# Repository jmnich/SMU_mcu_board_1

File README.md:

# SMU_mcu_board_1

MCU module for HtBlog Source Measure Unit

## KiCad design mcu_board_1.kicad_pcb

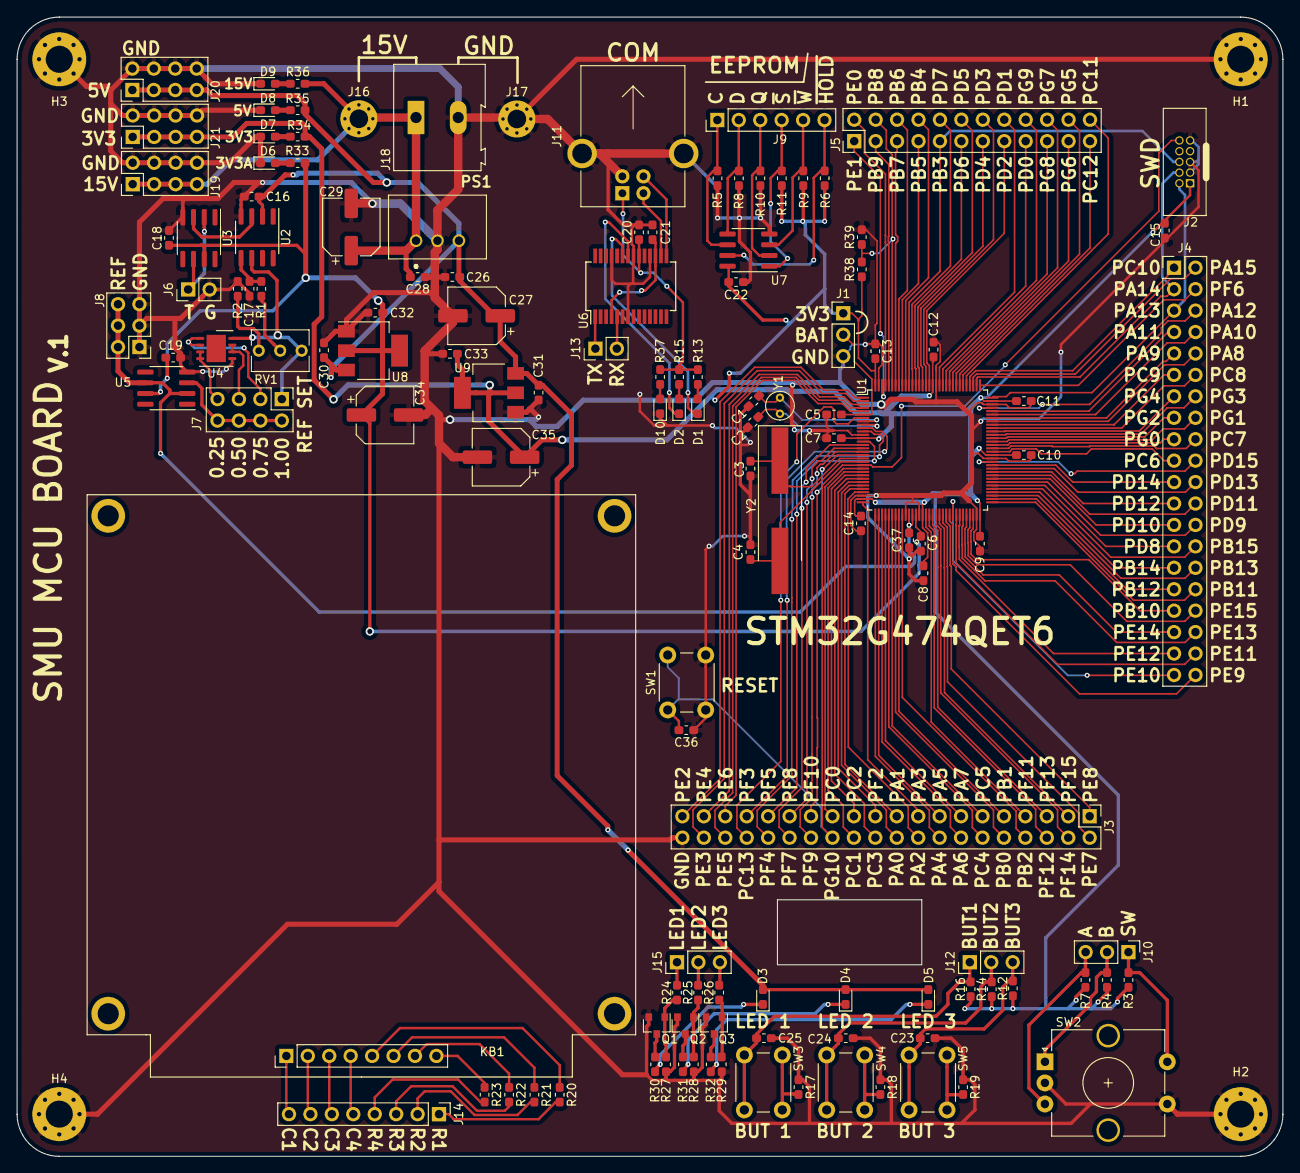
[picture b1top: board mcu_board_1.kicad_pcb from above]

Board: 2 copper layers, 150.0 x 135.0 mm, 133 parts (0 on the bottom side), 178 nets.

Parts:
C1, C2: 12p; C_0603_1608Metric_Pad1.05x0.95mm_HandSolder
C3, C4: 18p; C_0603_1608Metric_Pad1.05x0.95mm_HandSolder
C5, C15, C16, C17, C18, C19, C20, C21, C26, C28, C30, C31, C32, C33: 1u; C_0603_1608Metric_Pad1.05x0.95mm_HandSolder
C6, C7, C8, C9, C10, C11, C12, C13, C14, C22, C23, C24, C25, C36: 100n; C_0603_1608Metric_Pad1.05x0.95mm_HandSolder
C27, C29: 56u 25V; CP_Elec_6.3x5.9
C34, C35: 6.8u 25V; CP_Elec_6.3x5.9
C37: 1U; C_0603_1608Metric_Pad1.05x0.95mm_HandSolder
D1: R; LED_0603_1608Metric_Pad1.05x0.95mm_HandSolder
D2, D3, D4, D5: B; LED_0603_1608Metric_Pad1.05x0.95mm_HandSolder
D6, D7, D8, D9: LED G; LED_0603_1608Metric_Pad1.05x0.95mm_HandSolder
D10: G; LED_0603_1608Metric_Pad1.05x0.95mm_HandSolder
H1, H2, H3, H4: MountingHole_Pad; MountingHole_3.2mm_M3_Pad_Via
J1, J10, J12, J15: Conn_01x03; PinHeader_1x03_P2.54mm_Vertical
J2: ARM_SWD_10; JTAG_10pin_1.27_socket
J3, J4: Conn_02x20_Odd_Even; PinHeader_2x20_P2.54mm_Vertical
J5: Conn_02x12_Odd_Even; PinHeader_2x12_P2.54mm_Vertical
J6, J13: Conn_01x02; PinHeader_1x02_P2.54mm_Vertical
J7, J19, J20, J21: Conn_02x04_Odd_Even; PinHeader_2x04_P2.54mm_Vertical
J8: Conn_02x03_Odd_Even; PinHeader_2x03_P2.54mm_Vertical
J9: Conn_01x06; PinHeader_1x06_P2.54mm_Vertical
J11: USB-B_WE_61400416121; USB_B_Horizontal
J14: Conn_01x08; PinHeader_1x08_P2.54mm_Vertical
J16: +15V; MountingHole_2.2mm_M2_Pad_Via
J17: GND; MountingHole_2.2mm_M2_Pad_Via
J18: WE 691216710002; Terminal_block_WE691216710002
KB1: AK-1604-N; AK-1604-N-BBW
PS1: 173950536
Q1, Q2, Q3: 2N7002BK,215; SOT-23
R1: 470k 1%; R_0603_1608Metric_Pad1.05x0.95mm_HandSolder
R2, R17, R18, R19, R24, R25, R26: 1k 1%; R_0603_1608Metric_Pad1.05x0.95mm_HandSolder
R3, R4, R5, R6, R7, R8, R9, R10, R11, R12, R14, R16, R20, R21, R22, R23, R27, R28, R29, R39: 47k 1%; R_0603_1608Metric_Pad1.05x0.95mm_HandSolder
R13, R15, R30, R31, R32, R37: 10k 1%; R_0603_1608Metric_Pad1.05x0.95mm_HandSolder
R33, R35: 6k8; R_0603_1608Metric_Pad1.05x0.95mm_HandSolder
R34: 4k7; R_0603_1608Metric_Pad1.05x0.95mm_HandSolder
R36: 20k; R_0603_1608Metric_Pad1.05x0.95mm_HandSolder
R38: DNP; R_0603_1608Metric_Pad1.05x0.95mm_HandSolder
RV1: 10k; Potentiometer_Vishay_T73XW_Horizontal
SW1, SW3, SW4, SW5: SW_SPST; SW_PUSH_6mm_H4.3mm
SW2: Rotary_Encoder_Switch; RotaryEncoder_Alps_EC12E-Switch_Vertical_H20mm_CircularMoun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
U1: STM32G474QET6; LQFP-128_14x14mm_P0.4mm
U2: REF5040; SOIC-8_3.9x4.9mm_P1.27mm
U3, U5: OPA333AID; SOIC-8_3.9x4.9mm_P1.27mm
U4: 50k 0.1%; DFN-8-1EP_4x4mm_P0.8mm_EP2.3x3.24mm
U6: FT232RL; SSOP-28_5.3x10.2mm_P0.65mm
U7: M95M01-R; SOIC-8_3.9x4.9mm_P1.27mm
U8, U9: AMS1117-3.3; SOT-223-3_TabPin2
Y1: 32.7680kHz; Crystal_C38-LF_D3.0mm_L8.0mm_Vertical
Y2: 10MHz; Crystal_SMD_HC49-SD_HandSoldering

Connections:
+3.3VA: C6.2, C18.2, C19.2, C32.1, C34.1, R33.1, U1.45, U3.7, U5.7, U8.2
+3V3: C7.2, C8.2, C9.2, C10.2, C11.2, C12.2, C13.2, C14.2, C15.1, C22.1, C33.1, C35.1, J1.1, J2.1, J21.1, J21.3, J21.5, J21.7, R3.1, R4.1, R6.1, R7.1, R9.1, R11.1, R12.1, R14.1, R16.1, R34.1, R38.1, U1.13, U1.31, U1.47, U1.64, U1.79, U1.95, U1.111, U1.128, U7.8, U9.2
+5V: C16.1, C26.1, C27.1, C30.1, C31.1, D3.2, D4.2, D5.2, J20.1, J20.3, J20.5, J20.7, PS1.3, R35.1, U2.2, U8.3, U9.3
+15V: C28.2, C29.1, J16.1, J18.1, J19.1, J19.3, J19.5, J19.7, PS1.1, R36.1
/Analog/1_4_REF: J7.7, U4.3, U4.4
/Analog/2_4_REF: J7.5, U4.6, U4.7
/Analog/3_4_REF: J7.3, U4.1, U4.2
/Analog/REF: J7.1, RV1.1, U2.6, U4.8
/REF: C37.2, J8.2, J8.4, J8.6, U1.43, U1.44, U5.2, U5.6
GND: C1.2, C2.2, C3.2, C4.2, C5.1, C6.1, C7.1, C8.1, C9.1, C10.1, C11.1, C12.1, C13.1, C14.1, C15.2, C16.2, C17.2, C18.1, C19.1, C20.2, C21.2, C22.2, C23.2, C24.2, C25.2, C26.2, C27.2, C28.1, C29.2, C30.2, C31.2, C32.2, C33.2, C34.2, C35.2, C36.1, C37.1, D6.1, D7.1, D8.1, D9.1, D10.1, H1.1, H2.1, H3.1, H4.1, J1.3, J2.3, J2.5, J2.9, J3.40, J6.2, J8.1, J8.3, J8.5, J11.4, J11.5, J17.1, J18.2, J19.2, J19.4, J19.6, J19.8, J20.2, J20.4, J20.6, J20.8, J21.2, J21.4, J21.6, J21.8, PS1.2, Q1.2, Q2.2, Q3.2, R2.2, R5.1, R8.1, R10.1, R17.1, R18.1, R19.1, R27.2, R28.2, R29.2, R39.2, SW1.2, SW2.C, SW2.S2, U1.12, U1.30, U1.42, U1.46, U1.63, U1.78, U1.94, U1.110, U1.127, U2.4, U3.4, U4.5, U5.4, U6.7, U6.18, U6.21, U6.25, U7.4, U8.1, U9.1
unnamed: C1.1, U1.8, Y1.1
unnamed: C2.1, U1.9, Y1.2
unnamed: C3.1, U1.19, Y2.1
unnamed: C4.1, U1.20, Y2.2
unnamed: C5.2, J1.2, U1.6
unnamed: C17.1, R1.1, U2.5
unnamed: C20.1, J11.1, R13.1, R15.1, R37.1, U6.20
unnamed: C21.1, U6.4, U6.17
unnamed: C23.1, J12.3, R12.2, SW5.1
unnamed: C24.1, J12.2, R14.2, SW4.1
unnamed: C25.1, J12.1, R16.2, SW3.1
unnamed: D1.1, U6.23
unnamed: D1.2, R13.2
unnamed: D2.1, U6.22
unnamed: D2.2, R15.2
unnamed: D3.1, R30.1
unnamed: D4.1, R31.1
unnamed: D5.1, R32.1
unnamed: D6.2, R33.2
unnamed: D7.2, R34.2
unnamed: D8.2, R35.2
unnamed: D9.2, R36.2
unnamed: D10.2, R37.2
unnamed: J6.1, U3.2, U3.6
unnamed: J7.2, J7.4, J7.6, J7.8, U5.3
unnamed: J9.1, R5.2, U7.6
unnamed: J9.2, R8.2, U7.5
unnamed: J9.3, R10.2, U7.2
unnamed: J9.4, R11.2, U7.1
unnamed: J9.5, R9.2, U7.3
unnamed: J9.6, R6.2, U7.7
unnamed: J10.1, R3.2, SW2.S1
unnamed: J10.2, R4.2, SW2.A
unnamed: J10.3, R7.2, SW2.B
unnamed: J11.2, U6.16
unnamed: J11.3, U6.15
unnamed: J13.1, U6.1
unnamed: J13.2, U6.5
unnamed: J14.1, R20.2
unnamed: J14.2, R21.2
unnamed: J14.3, R22.2
unnamed: J14.4, R23.2
unnamed: J14.5, KB1.4
unnamed: J14.6, KB1.3
unnamed: J14.7, KB1.2
unnamed: J14.8, KB1.1
unnamed: J15.1, R24.2
unnamed: J15.2, R25.2
unnamed: J15.3, R26.2
unnamed: KB1.5, R20.1
unnamed: KB1.6, R21.1
unnamed: KB1.7, R22.1
unnamed: KB1.8, R23.1
unnamed: Q1.1, R24.1, R27.1
unnamed: Q1.3, R30.2
unnamed: Q2.1, R25.1, R28.1
unnamed: Q2.3, R31.2
unnamed: Q3.1, R26.1, R29.1
unnamed: Q3.3, R32.2
unnamed: R1.2, RV1.2
unnamed: R2.1, RV1.3
unnamed: R17.2, SW3.2
unnamed: R18.2, SW4.2
unnamed: R19.2, SW5.2
unnamed: U2.3, U3.3
PA0: J3.20, U1.27
PA1: J3.19, U1.28
PA2: J3.18, U1.29
PA3: J3.17, U1.32
PA4: J3.16, U1.33
PA5: J3.15, U1.34
PA6: J3.14, U1.35
PA7: J3.13, U1.36
PA8: J4.10, U1.89
PA9: J4.9, U1.90
PA10: J4.8, U1.91
PA11: J4.7, U1.92
PA12: J4.6, U1.93
PA13: J2.2, J4.5, U1.96
PA14: J2.4, J4.3, U1.98
PA15: J4.2, U1.99
PB0: J3.10, U1.39
PB1: J3.9, U1.40
PB2: J3.8, U1.41
PB3: J2.6, J5.9, U1.118
PB4: J5.8, U1.119
PB5: J5.7, U1.120
PB6: J5.6, U1.121
PB7: J5.5, U1.122
PB8: J5.4, R38.2, R39.1, U1.123
PB9: J5.3, U1.124
PB10: J4.33, U1.62
PB11: J4.32, U1.65
PB12: J4.31, U1.66
PB13: J4.30, U1.67
PB14: J4.29, U1.68
PB15: J4.28, U1.69
PC0: J3.25, U1.22
PC1: J3.24, U1.23
PC2: J3.23, U1.24
PC3: J3.22, U1.25
PC4: J3.12, U1.37
PC5: J3.11, U1.38
PC6: J4.19, U1.80
PC7: J4.18, U1.81
PC8: J4.12, U1.87
PC9: J4.11, U1.88
PC10: J4.1, U1.100
PC11: J5.24, U1.101
PC12: J5.23, U1.102
PC13: J3.34, U1.7
PD0: J5.17, U1.108
PD1: J5.16, U1.109
PD2: J5.15, U1.112
PD3: J5.14, U1.113
PD4: J5.13, U1.114
PD5: J5.12, U1.115
PD6: J5.11, U1.116
PD7: J5.10, U1.117
PD8: J4.27, U1.70
PD9: J4.26, U1.71
PD10: J4.25, U1.72
PD11: J4.24, U1.73
PD12: J4.23, U1.74
PD13: J4.22, U1.75
PD14: J4.21, U1.76
PD15: J4.20, U1.77
PE0: J5.2, U1.125
PE1: J5.1, U1.126
PE2: J3.39, U1.1
PE3: J3.38, U1.2
PE4: J3.37, U1.3
PE5: J3.36, U1.4
PE6: J3.35, U1.5
PE7: J3.2, U1.53
PE8: J3.1, U1.54
PE9: J4.40, U1.55
PE10: J4.39, U1.56
PE11: J4.38, U1.57
PE12: J4.37, U1.58
PE13: J4.36, U1.59
PE14: J4.35, U1.60
PE15: J4.34, U1.61
PF2: J3.21, U1.26
PF3: J3.33, U1.10
PF4: J3.32, U1.11
PF5: J3.31, U1.14
PF6: J4.4, U1.97
PF7: J3.30, U1.15
PF8: J3.29, U1.16
PF9: J3.28, U1.17
PF10: J3.27, U1.18
PF11: J3.7, U1.48
PF12: J3.6, U1.49
PF13: J3.5, U1.50
PF14: J3.4, U1.51
PF15: J3.3, U1.52
PG0: J4.17, U1.82
PG1: J4.16, U1.83
PG2: J4.15, U1.84
PG3: J4.14, U1.85
PG4: J4.13, U1.86
PG5: J5.22, U1.103
PG6: J5.21, U1.104
PG7: J5.20, U1.105
PG8: J5.19, U1.106
PG9: J5.18, U1.107
PG10: C36.2, J2.10, J3.26, SW1.1, U1.21

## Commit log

2020-11-08 schematics done and moved to repo
2020-11-08 MCU prepped for fanout
2020-11-09 done and done
2020-11-09 production pack generated
